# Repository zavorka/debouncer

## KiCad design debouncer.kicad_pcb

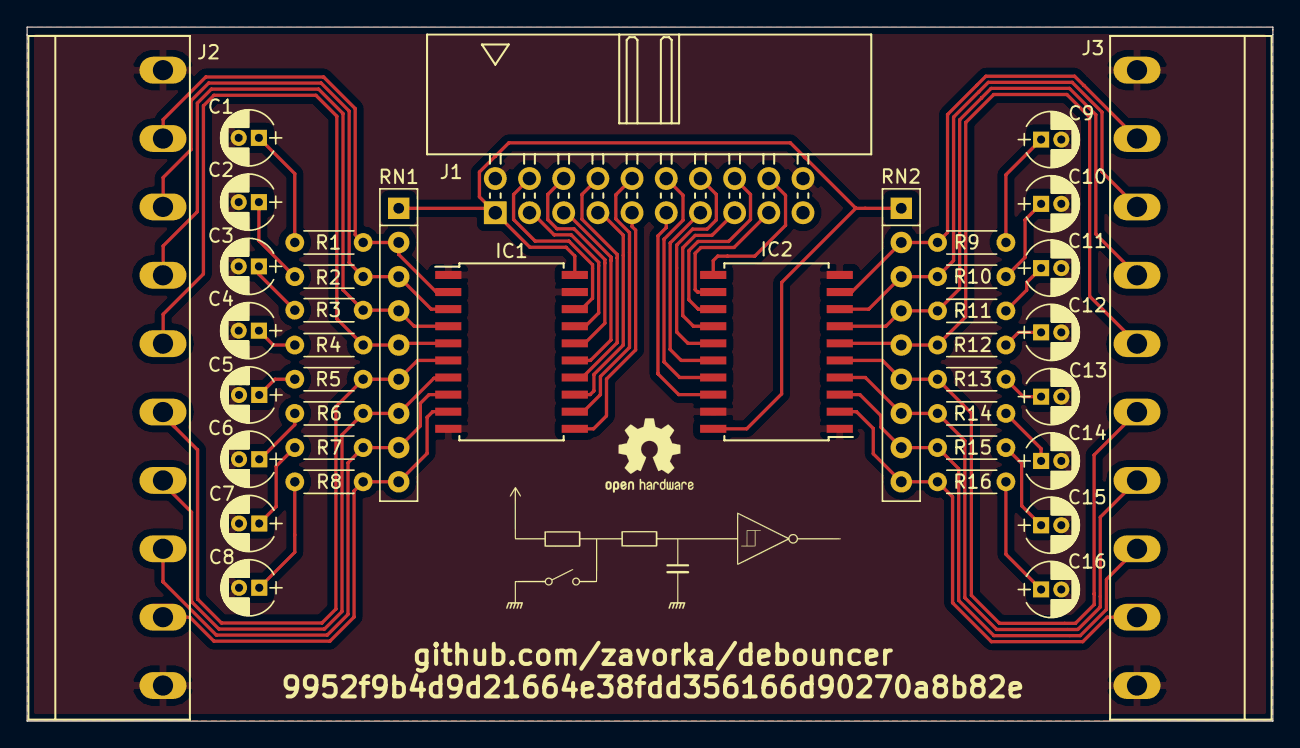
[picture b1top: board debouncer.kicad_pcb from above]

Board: 2 copper layers, 92.6 x 51.6 mm, 39 parts (0 on the bottom side), 50 nets.

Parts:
C1, C2, C3, C4, C5, C6, C7, C8, C9, C10, C11, C12, C13, C14, C15, C16: 1u; CP_Radial_D4.0mm_P1.50mm
IC1, IC2: 74HC7540; SOIC-20W_7.5x12.8mm_Pitch1.27mm
J1: Conn_02x10_Odd_Even; Multicomp_MC9A22-2034_2x10x2.54mm_Angled
J2, J3: Screw_Terminal_01x10; PTR_STLZ950_10-5_08
R1, R2, R3, R4, R5, R6, R7, R8, R9, R10, R11, R12, R13, R14, R15, R16: 7k5; R_Axial_DIN0204_L3.6mm_D1.6mm_P5.08mm_Horizontal
RN1, RN2: 1k2; R_Array_SIP9

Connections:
+3V3: IC1.20, IC2.20, J1.1, RN1.1, RN2.1
GND: C1.2, C2.2, C3.2, C4.2, C5.2, C6.2, C7.2, C8.2, C9.2, C10.2, C11.2, C12.2, C13.2, C14.2, C15.2, C16.2, IC1.1, IC1.10, IC1.19, IC2.1, IC2.10, IC2.19, J1.2, J1.20, J2.1, J2.10, J3.1, J3.10
unnamed: C1.1, R1.1
unnamed: C2.1, R2.1
unnamed: C3.1, R3.1
unnamed: C4.1, R4.1
unnamed: C5.1, R5.1
unnamed: C6.1, R6.1
unnamed: C7.1, R7.1
unnamed: C8.1, R8.1
unnamed: C9.1, R9.1
unnamed: C10.1, R10.1
unnamed: C11.1, R11.1
unnamed: C12.1, R12.1
unnamed: C13.1, R13.1
unnamed: C14.1, R14.1
unnamed: C15.1, R15.1
unnamed: C16.1, R16.1
unnamed: IC1.2, J2.2, R1.2, RN1.2
unnamed: IC1.3, J2.3, R2.2, RN1.3
unnamed: IC1.4, J2.4, R3.2, RN1.4
unnamed: IC1.5, J2.5, R4.2, RN1.5
unnamed: IC1.6, J2.6, R5.2, RN1.6
unnamed: IC1.7, J2.7, R6.2, RN1.7
unnamed: IC1.8, J2.8, R7.2, RN1.8
unnamed: IC1.9, J2.9, R8.2, RN1.9
unnamed: IC1.11, J1.9
unnamed: IC1.12, J1.10
unnamed: IC1.13, J1.7
unnamed: IC1.14, J1.8
unnamed: IC1.15, J1.5
unnamed: IC1.16, J1.6
unnamed: IC1.17, J1.3
unnamed: IC1.18, J1.4
unnamed: IC2.2, J3.2, R16.2, RN2.9
unnamed: IC2.3, J3.3, R15.2, RN2.8
unnamed: IC2.4, J3.4, R14.2, RN2.7
unnamed: IC2.5, J3.5, R13.2, RN2.6
unnamed: IC2.6, J3.6, R12.2, RN2.5
unnamed: IC2.7, J3.7, R11.2, RN2.4
unnamed: IC2.8, J3.8, R10.2, RN2.3
unnamed: IC2.9, J3.9, R9.2, RN2.2
unnamed: IC2.11, J1.18
unnamed: IC2.12, J1.17
unnamed: IC2.13, J1.16
unnamed: IC2.14, J1.15
unnamed: IC2.15, J1.14
unnamed: IC2.16, J1.13
unnamed: IC2.17, J1.12
unnamed: IC2.18, J1.11

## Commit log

2018-04-05 initial
